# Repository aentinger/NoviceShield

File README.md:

💾 Novice Shield
================

# 📸 Image

# 📂 Description

The LXRobotics Novice Shield was developed to provide Arduino beginners with a smooth introduction of how to interface various sensors/actuators with an Arduino. This is achieved by providing actuators and sensors frequently encountered in Arduino applications such as light sensors, temperature sensors, switches, relays, potentiometers, LEDs etc. Numerous sample programs illustrate how the respective sensors or actuators can be controlled.

**Features**

* LED traffic light system consisting of red, yello and green LED
* 2 push buttons
* 2 RC servo connectors for controlling RC servos
* Fixed and variable voltage divider
* Light sensor (Light Dependent Resistor)
* 2 Temperature sensors: PTC und NTC
* Relay with Optocoupler
* Relay facts:
  * Max. current: 10 A
  * Max. DC voltage: 24 V DC
  * Max. AC voltage: 250 V AC
  * Relay-Typ: SPDT (Single Pole commutator)
* Numerous example program

# 🎥 [Video](images/novice_shield_demo.mp4)

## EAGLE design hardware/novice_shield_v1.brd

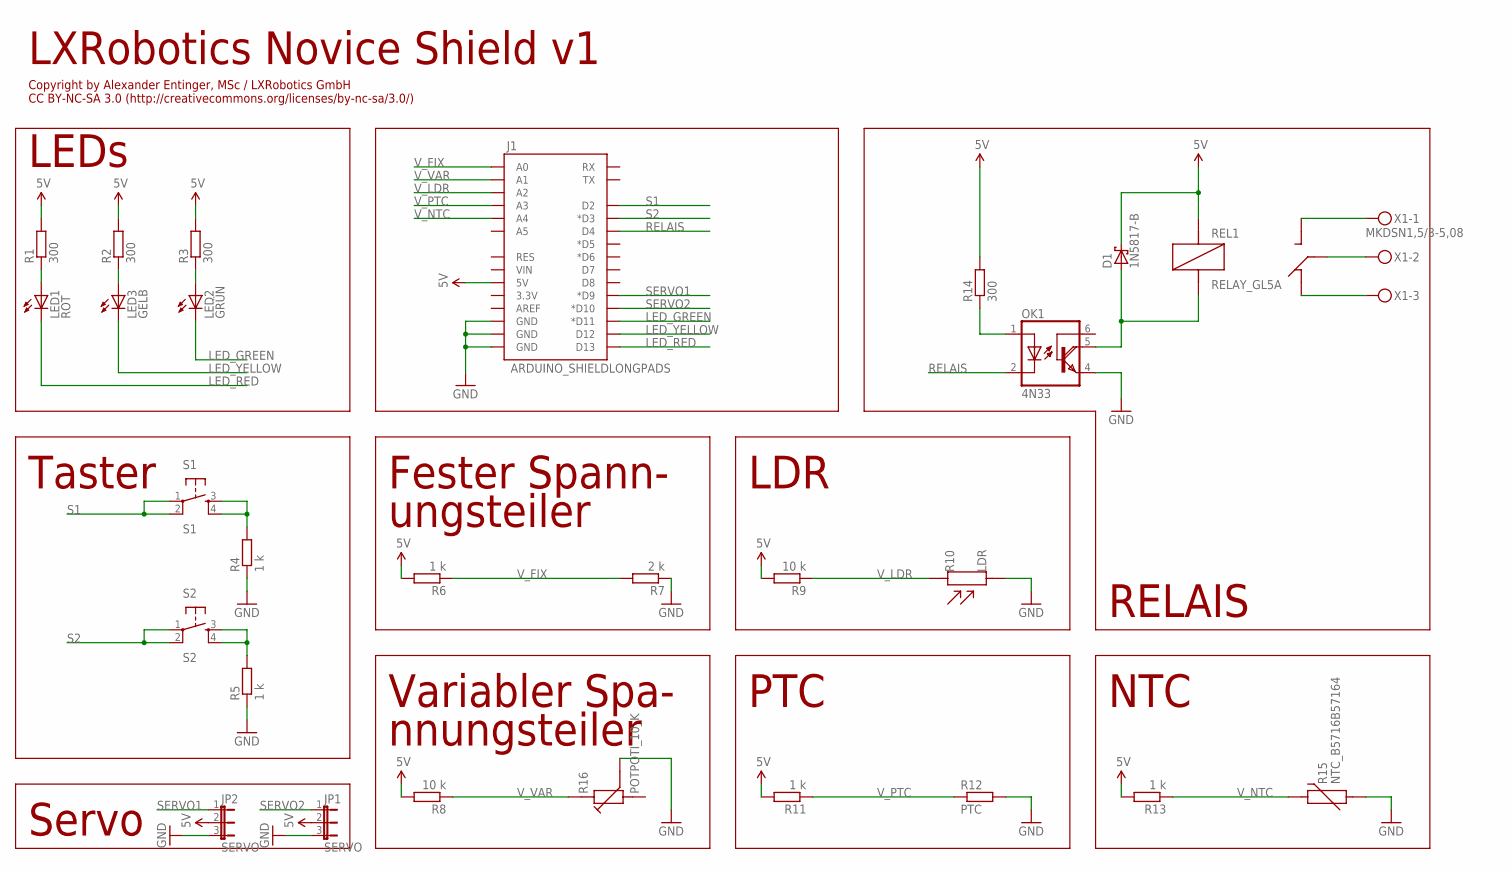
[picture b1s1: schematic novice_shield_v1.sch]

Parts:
D1: 1N5817-B; DO41-7.6
J1: ARDUINO_SHIELDLONGPADS; DUEMILANOVE_SHIELD_LONGPADS
JP1, JP2: SERVO; JP2
LED1: ROT; LED5MM
LED2: GRÜN; LED5MM
LED3: GELB; LED5MM
OK1: 4N33; DIL06
R1, R2, R3, R14: 300; 0204/5
R4, R5, R6, R11, R13: 1 k; 0204/5
R7: 2 k; 0204/5
R8, R9: 10 k; 0204/5
R10: LDR
R12: PTC; 0207/10
R15: NTC_B5716B57164; NTC_5MM_RADIAL
R16: POTPOTI_10_K; POT_10K
REL1: RELAY_GL5A
S1: S1; TACTILE-PTH
S2: S2; TACTILE-PTH
X1: MKDSN1,5/3-5,08

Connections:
5V: D1.C, J1.5V, JP1.2, JP2.2, R1.2, R2.2, R3.2, R6.2, R8.2, R9.2, R11.2, R13.2, R14.2, REL1.R2 (R2_COIL1)
GND: J1.GND@0 (GND), J1.GND@1 (GND), J1.GND@2 (GND), JP1.3, JP2.3, OK1.4 (E), R4.1, R5.1, R7.1, R10.P$2, R12.2, R15.P$2 (2), R16.VAR
LED_GREEN: J1.D11 (*D11), LED2.K (C)
LED_RED: J1.D13, LED1.K (C)
LED_YELLOW: J1.D12, LED3.K (C)
unnamed: LED1.A, R1.1
unnamed: LED3.A, R2.1
unnamed: LED2.A, R3.1
unnamed: R4.2, S1.3, S1.4
unnamed: R5.2, S2.3, S2.4
unnamed: REL1.R4 (R4_SW), X1.3
unnamed: REL1.R1 (R1_COMMON), X1.2
unnamed: REL1.R3 (R3_SW), X1.1
unnamed: OK1.1 (A), R14.1
unnamed: D1.A, OK1.5 (COL), REL1.R5 (R5_COIL2)
RELAIS: J1.D4, OK1.2 (C)
S1: J1.D2, S1.1, S1.2
S2: J1.D3 (*D3), S2.1, S2.2
SERVO1: J1.D9 (*D9), JP2.1
SERVO2: J1.D10 (*D10), JP1.1
V_FIX: J1.A0, R6.1, R7.2
V_LDR: J1.A2, R9.1, R10.P$1
V_NTC: J1.A4, R13.1, R15.P$1 (1)
V_PTC: J1.A3, R11.1, R12.1
V_VAR: J1.A1, R8.1, R16.S

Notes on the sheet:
LEDs
Taster
Fester Spann-
ungsteiler
Variabler Spa-
nnungsteiler
LDR
Servo
PTC
NTC
RELAIS
LXRobotics Novice Shield v1
Copyright by Alexander Entinger, MSc / LXRobotics GmbH CC BY-NC-SA 3.0 (http://creativecommons.org/licenses/by-nc-sa/3.0/)

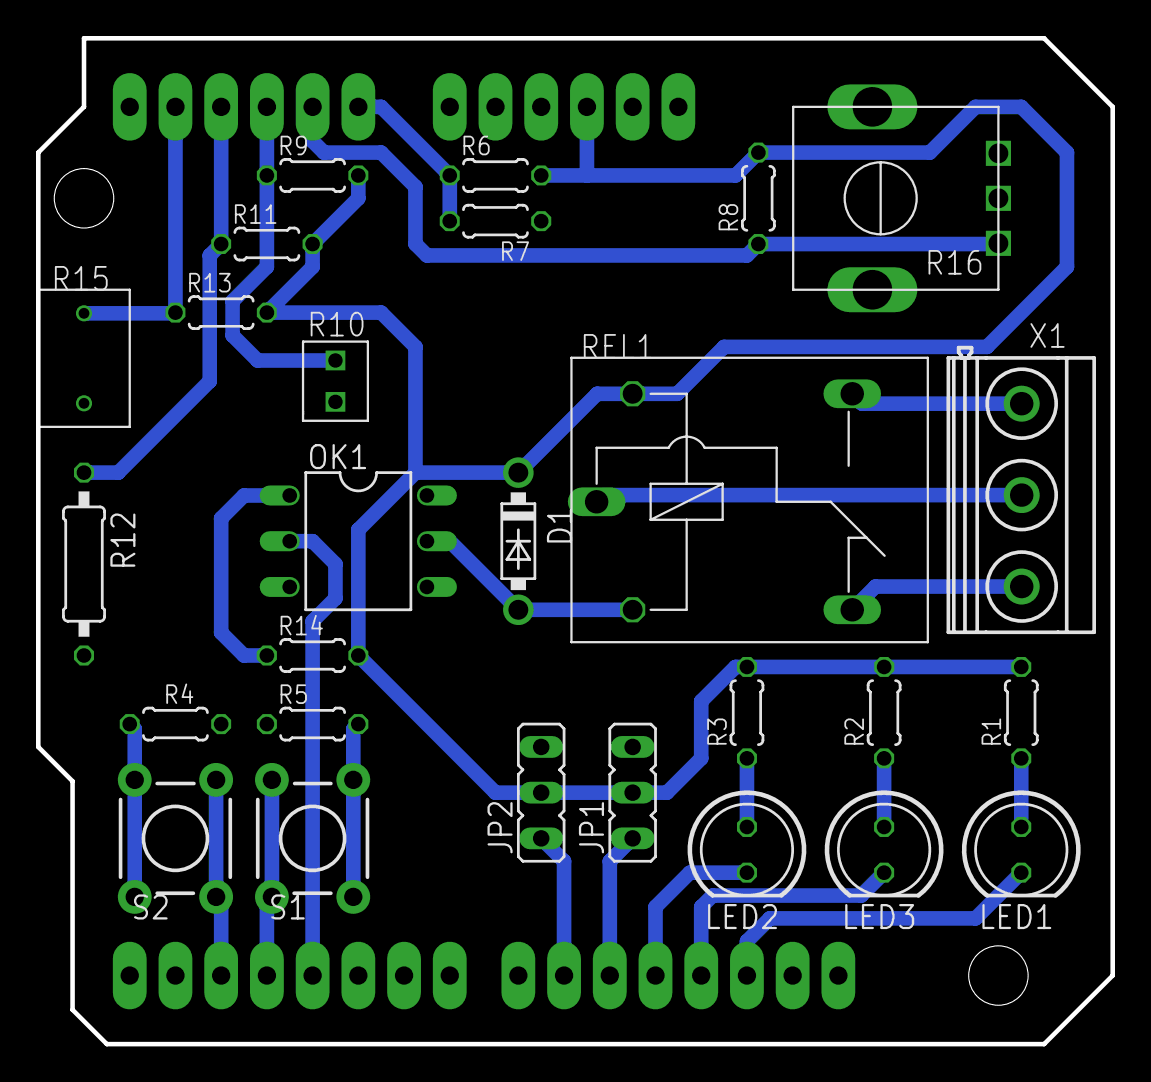
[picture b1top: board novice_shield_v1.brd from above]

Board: 2 copper layers, 59.7 x 55.9 mm, 28 parts (0 on the bottom side), 25 nets.

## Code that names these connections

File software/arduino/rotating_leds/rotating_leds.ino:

/**
 * @author Alexander Entinger, MSc / LXRobotics
 * @brief this sketch demonstrates how to control the leds of the LXRobotics Novice Shield
 * @file rotating_leds.ino
 */

static int const led_green_pin = 11; // D11
static int const led_yellow_pin = 12; // D12
static int const led_red_pin = 13; // D13

void setup() {
  // configure the led pins as outputs
  pinMode(led_green_pin, OUTPUT);
  pinMode(led_yellow_pin, OUTPUT);
  pinMode(led_red_pin, OUTPUT);
  // turn of the leds
  turn_off_red();
  turn_off_yellow();
  turn_off_green();
}

void turn_on_red() {
  digitalWrite(led_red_pin, LOW);
}
void turn_off_red() {
  digitalWrite(led_red_pin, HIGH);
}
void turn_on_yellow() {
  digitalWrite(led_yellow_pin, LOW);
}
void turn_off_yellow() {
  digitalWrite(led_yellow_pin, HIGH);
}
void turn_on_green() {
  digitalWrite(led_green_pin, LOW);
}
void turn_off_green() {
  digitalWrite(led_green_pin, HIGH);
}

void loop() {
  turn_off_green();
  turn_on_red();
  delay(100);
  turn_on_yellow();
  turn_off_red();
  delay(100);
  turn_on_green();
  turn_off_yellow();
  delay(100);
}

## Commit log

2014-06-18 checking in initial demo examples and schematic
2017-06-27 Adding hardware + images
2025-03-26 Upload BOM.
2025-03-26 Upload demo video.
2025-03-26 Pretty up README.
2025-03-26 Use relative links.

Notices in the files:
README.md:
License: CC BY-NC-SA 4.0
parts and their libraries:
SparkFun-Boards: Licensing: CC v3.0 Share-Alike You are welcome to use this library for commercial purposes.
